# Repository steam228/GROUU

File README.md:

# GROUU - Modular Open Agriculture

## Overview
GROUU enables the implementation of Precision Agriculture / Automation in the context of personal or small scale agricultures.
At the moment, the development goals for GROUU V2 is to implement a local/edge server based on a raspberry pi or other linux mini computer, a sensor node template with wifi communication and other with LoraWAN communication. The same for two actuator templates.
when this basic infrastructure is designed we will apply it to personal contexts in order to test it.
This process will generate new repositores.
This Git repository also archives the personal development and learning process behind the project and research done throught it.

**Let us know if you want to collaborate**

## Table of Contents
1. [GROUU V3 — WellBouy (well-water LoRaWAN node)](#grouu-v3--wellbouy)
1. [GROUU V2](#grouu-v2)
   - [Server Documentation - GROUU Server V2 Configuration](#server-documentation)
   - [Sensor Modules Documentation - GROUU V2 Sensor Modules Configuration](#sensor-modules-documentation)
   - [Actuator Modules Documentation - GROUU V2 Sensor Actuator Configuration](#actuator-modules-documentation)
2. [GROUU V1](#grouu-v1)
   - [Modules V1 - ESP12 Based Version](#modules-v1---esp12-based-version)
   - [Server Configuration - Raspberry Pi Zero W](#server-configuration---raspberry-pi-zero-w)
3. [Archived Projects](#archived-projects)
4. [References](#references)

## GROUU V3 — WellBouy

A well-water-quality LoRaWAN sensor node (**XIAO ESP32-S3 + Wio-SX1262**): reads
water **temperature / TDS / turbidity / pH**, encodes them as CayenneLPP, and
uplinks to **The Things Network** (EU868, OTAA) while deep-sleeping between
readings. On a **Raspberry Pi** the data flows TTN → Node-RED → InfluxDB 2 →
Grafana, and a small public dashboard renders it live.

📁 [/ARDUINO/GROUU_V3/](/ARDUINO/GROUU_V3/) · 📊 live dashboard: **https://grouuwell01.hacktoimprove.com**

Full docs — hardware, firmware bring-up, calibration, data pipeline, the web
dashboard, and the dedicated atopile PCB — are in
[ARDUINO/GROUU_V3/README.md](/ARDUINO/GROUU_V3/README.md).

## GROUU V2

### Sensor Modules Documentation
GROUU V2 Sensor Modules Configuration

[/ARDUINO/GROUU_V2/](/ARDUINO/GROUU_V2/)

#### GROUU V2 WiFi Sensor Node Template

#### GROUU V2 LoRA Sensor Node Template

### Actuator Modules Documentation
GROUU V2 Sensor Actuator Configuration

### Server Documentation
GROUU Server V2 Configuration(GROUU Stack V1)

The GROUU Stack V1 (part of GROUU V2) provides an advanced foundation for your open-source IoT farming project:

1. Mosquitto for MQTT messaging between your farming sensors and the system
2. Node-RED for creating workflows and processing data from your farm
3. InfluxDB for storing time-series data from your agricultural sensors
4. Grafana for creating dashboards to visualize your farming data

#### GROUU Stack V1 Installation and Deployment Tutorial

This guide will help you set up the GROUU Stack V1, an open-source IoT solution for personal and small-scale farming.

##### 1. Install Docker

First, we need to install Docker on your Linux system:

```bash
# Update and upgrade the system
sudo apt update && sudo apt upgrade -y

# Install required packages
sudo apt install -y apt-transport-https ca-certificates curl gnupg lsb-release

# Add Docker's official GPG key and set up the repository
curl -fsSL https://get.docker.com -o get-docker.sh
sudo sh get-docker.sh

# Add your user to the docker group
sudo usermod -aG docker $USER

# Enable Docker to start on boot
sudo systemctl enable docker
```

Log out and log back in for the group changes to take effect.

##### 2. Install Portainer

Now, let's install Portainer:

```bash
# Create volume for Portainer
docker volume create portainer_data

# Install Portainer CE
docker run -d -p 8000:8000 -p 9000:9000 --name=portainer --restart=always \
  -v /var/run/docker.sock:/var/run/docker.sock \
  -v portainer_data:/data \
  portainer/portainer-ce
```

##### 3. Access Portainer

Open a web browser and navigate to `http://your-server-ip:9000`. You'll be prompted to create an admin user.

##### 4. Deploy the GROUU Stack V1

1. In Portainer, go to "Stacks" and click "Add stack".
2. Name your stack "GROUU-Stack-V1".
3. In the "Web editor" tab, paste the GROUU Stack V1 configuration:

```yaml
version: '3'

services:
  mosquitto:
    image: eclipse-mosquitto:latest
    ports:
      - "1883:1883"
    volumes:
      - mosquitto-config:/mosquitto/config
      - mosquitto-data:/mosquitto/data
      - mosquitto-log:/mosquitto/log
    restart: always

  nodered:
    image: nodered/node-red:latest
    ports:
      - "1880:1880"
    volumes:
      - nodered-data:/data
    restart: always

  influxdb:
    image: influxdb:latest
    ports:
      - "8086:8086"
    volumes:
      - influxdb-data:/var/lib/influxdb
    environment:
      - INFLUXDB_DB=grouudb
      - INFLUXDB_ADMIN_USER=admin
      - INFLUXDB_ADMIN_PASSWORD=grouuadmin  # Remember to change this password
    restart: always

  grafana:
    image: grafana/grafana:latest
    ports:
      - "3000:3000"
    volumes:
      - grafana-data:/var/lib/grafana
    restart: always

volumes:
  mosquitto-config:
  mosquitto-data:
  mosquitto-log:
  nodered-data:
  influxdb-data:
  grafana-data:
```

4. Click "Deploy the stack".

##### 5. Post-Deployment Steps

After deploying the GROUU Stack V1, you can access its components:

1. Node-RED (for flow-based programming): `http://your-server-ip:1880`
2. InfluxDB (time-series database): Use the InfluxDB CLI or API at `http://your-server-ip:8086`
3. Grafana (for visualization): `http://your-server-ip:3000`
4. Mosquitto (MQTT broker): Use an MQTT client to connect to `your-server-ip:1883`

Remember to replace `your-server-ip` with your actual server IP address.

##### 6. Security Considerations

- Change default passwords for all services in the GROUU Stack V1
- Use SSL/TLS for MQTT if exposing your farming data to the internet
- Set up proper firewalls and access controls
- Regularly update all containers and the host system to ensure your farming data remains secure

Congratulations! You now have the GROUU Stack V1 up and running for your personal or small-scale farming IoT project.

#### Manual Installation Guide

If you prefer not to use the stack configuration, you can follow these steps for manual installation:

#### 1. Install Docker

Follow the Docker installation steps from the stack installation guide above.

#### 2. Install Portainer CE and Portainer Agent

```bash
# Create volume for Portainer
docker volume create portainer_data

# Install Portainer CE
docker run -d -p 8000:8000 -p 9000:9000 --name=portainer --restart=always -v /var/run/docker.sock:/var/run/docker.sock -v portainer_data:/data portainer/portainer-ce

# Install Portainer Agent
docker run -d -p 9001:9001 --name portainer_agent --restart=always -v /var/run/docker.sock:/var/run/docker.sock -v /var/lib/docker/volumes:/var/lib/docker/volumes portainer/agent
```

#### 3. Install Containers via Portainer

Access Portainer web interface at `http://your-server-ip:9000` and follow these steps for each container:

##### 3.1 Mosquitto (MQTT Broker)

1. Go to "Containers" > "Add container"
2. Name: mosquitto
3. Image: eclipse-mosquitto:latest
4. Port mapping: 1883:1883
5. Volumes:
    - /path/to/mosquitto/config:/mosquitto/config
    - /path/to/mosquitto/data:/mosquitto/data
    - /path/to/mosquitto/log:/mosquitto/log

##### 3.2 Node-RED

1. Go to "Containers" > "Add container"
2. Name: nodered
3. Image: nodered/node-red:latest
4. Port mapping: 1880:1880
5. Volumes:
    - /path/to/nodered/data:/data

##### 3.3 InfluxDB

1. Go to "Containers" > "Add container"
2. Name: influxdb
3. Image: influxdb:latest
4. Port mapping: 8086:8086
5. Volumes:
    - /path/to/influxdb/data:/var/lib/influxdb
6. Environment variables:
    - INFLUXDB_DB=mydb
    - INFLUXDB_ADMIN_USER=admin
    - INFLUXDB_ADMIN_PASSWORD=adminpassword

##### 3.4 Grafana

1. Go to "Containers" > "Add container"
2. Name: grafana
3. Image: grafana/grafana:latest
4. Port mapping: 3000:3000
5. Volumes:
    - /path/to/grafana/data:/var/lib/grafana

#### 4. Post-Installation Steps

Follow the post-deployment steps and security considerations from the stack installation guide above.

## GROUU V1

### Modules V1 - ESP12 Based Version
*Under development - design (boards, enclosures), firmware (Arduino)*

#### Types:
- Core
- S modules (wireless sensors)
- A modules (actuator modules)

#### Development Goals
- The way the module is powered is not yet fully defined: All should have batteries (3.3V _____ Amps), some should have only this as power source and be periodically charged (induction most probably), and others, can be connected to a power source (solar, network, wind...) for constant charging;
- A power source (ex: solar panel) can be a module on its own and an induction charger can be another module (tbd - to be designed);
- The following code:
```cpp
const String Instalation = "myFarm"; //Where is it?
const String IDCODE = "1"; //number your probe
const String TYPE = "SoilProbe"; //choose type
const String Host = "Grouu" + Instalation + TYPE + IDCODE; //just change if it is not grouu and you're adapting the code for something else
const char * OTA_PASSWORD  = "yourpasswordhere";
```
will allow you to set a hostname (Host) - These are the only parameters you should have to change before injecting the firmware on your board (we should work on an even simpler method);

- This hostname (`const String Host`):
  1. will be the name of the network the device generates each time it is not able to connect to any wireless network;
  2. Will identify the MQTT addresses being used by that type of device (expl: `HostName/Sensor/Moist1`);

- There shouldn't be a limit for the amount of modules developed nor used. The scale and context should dictate these options.
- All Explorations, independently from the context or scale should be considered valid data generators;

#### Call for Collaboration

It is permanent, develop whatever you want whenever you want!

#### Current Modules

##### Soil Probe

- The soil probe reads Soil Moisture and Soil Temperature;
- You can add as many as you want in order to measure these in as many points as you wish.

###### Design
- eagleCAD: [Link to eagleCAD files]
- Fusion 3D (plastic 3D print Enclosure): [Link to Fusion 3D files]

###### Code
- Arduino IDE Firmware: [Link to Arduino code]

##### Water Router

- The water router uses a standard 1 in 4 out electrovalves from a washing machine. You should also decrease the water pressure on the outputs for microirrigation.
- You can use this directly to the network or after a motor (be careful with the pressure in compatibility). You can add as many as you want in the system.

###### Design
- eagleCAD: [Link to eagleCAD files]
- Fusion 3D (plastic 3D print Enclosure): [Link to Fusion 3D files]

###### Code
- Arduino IDE Firmware: [Link to Arduino code]

##### Core

- Core is the local server. Right now is mostly a test hub where the data from the networked servers is received and processed.
- We are using Node-Red but all collaboration is welcomed!

###### Design
Right now we are using a standard Raspberry case.

### Server Configuration - Raspberry Pi Zero W

#### Configuring Raspberry Pi Zero W as server

1. Configuring the Pi: [Tutorial Link](https://core-electronics.com.au/tutorials/raspberry-pi-zerow-headless-wifi-setup.html)

2. Accessing through ssh on mac or linux terminal: [Tutorial Link](https://www.raspberrypi.org/documentation/remote-access/ssh/unix.md)

3. Upgrade Node-Red and Node.js
```bash
sudo apt-get update
sudo apt-get upgrade
bash <(curl -sL https://raw.githubusercontent.com/node-red/raspbian-deb-package/master/resources/update-nodejs-and-nodered)
sudo systemctl enable nodered.service
```
- Connect to Raspberry Pi Node-red console through your browser by accessing `http://"raspipaddress":1880`

- Install Mosquitto MQTT broker
```bash
sudo apt-get install mosquitto
```

Some instructions on how to test here: [Instructables Tutorial](https://www.instructables.com/id/Installing-MQTT-BrokerMosquitto-on-Raspberry-Pi/)

4. Other useful links:
   Security: manage permissions on node-red tutorial - [YouTube Tutorial](https://www.youtube.com/watch?v=GeN7g4bdHiM)

## Archived Projects

### Main Soil Probe REV0
Developed at the Habibi Works (Ioannina, Greece) CultiMake Workshop - P2PLab

#### Design
- eagleCAD: A provisional board (not working!!) is on [/BOARDS/soilProbe/Archive](/BOARDS/soilProbe/Archive)
- For this example, a nodeMCU dev board was used and tested at the workshop (see Habibi.Works [Workshop Journal](WORKSHOP/habibiWorksJuly2018/workshopJournal.md))
- Enclosure: A standard plastic box was used for demo purposes.

This board includes:
- 1 x 4 male header for DHT22 Temperature and Humidity Sensor
- 1 x 3 male header for DS18B20 (encapsulated version for Soil Temperature)
- 2 x 2 male header connections for Moisture 10k with Two probes
- 1 led (no usage yet, mostly for debug purposes)
- 1 ftdi set headers
- 1 voltage converter 12V - 3,3V
- 1 x 2 screw headers to add solar panel + battery (maybe connect solar battery pack now)

#### Code
Arduino IDE Firmware: [/ARDUINO/habibiWorksJuly2018-WS/grouu-irr](/ARDUINO/habibiWorksJuly2018-WS/grouu-irr)

### GROUU Greenhouse

#### Design
- SolidWorks files for the complete Structure (to be added) - also check constructive system (levosystems.com)
- Photos (soon)
- Other Diagrams (soon)

#### Code
Arduino Yun code: [/ARCHIVE/arduino/GROUU_GREENHOUSE_0/](/ARCHIVE/arduino/GROUU_GREENHOUSE_0/)

## References

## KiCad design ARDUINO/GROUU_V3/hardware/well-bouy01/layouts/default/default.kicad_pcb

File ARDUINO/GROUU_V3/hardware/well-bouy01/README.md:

# well-bouy01

Wooohooo a new package!

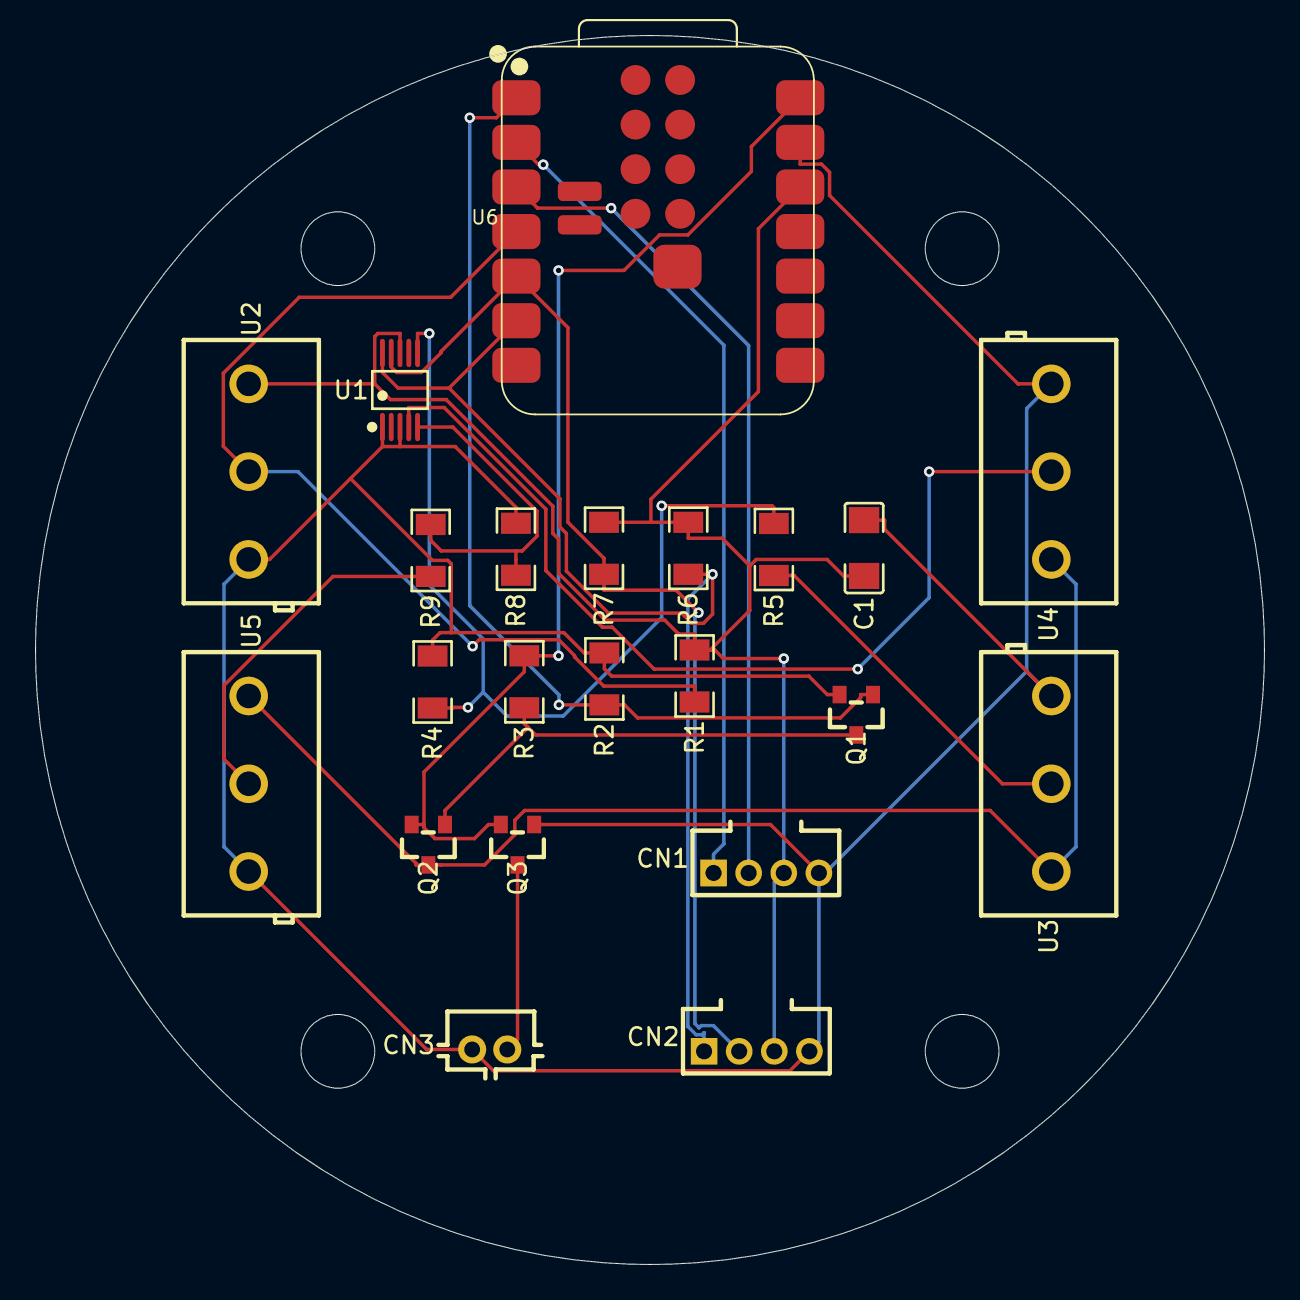
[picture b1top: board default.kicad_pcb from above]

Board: 2 copper layers, 70.0 x 70.0 mm, 22 parts (0 on the bottom side), 17 nets.

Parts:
C1: 100nF ±10%; C1206
CN1, CN2: CONN-TH_4P-P2.00_L5.1-W10.0
CN3: CONN-TH_B2B-PH-K-S
Q1, Q2, Q3: SOT-23_L2.9-W1.3-P1.90-LS2.4-BR
R1, R6, R7: 4.7kΩ ±1%; R1206
R2, R3: 100kΩ ±5%; R1206
R4: 18kΩ ±1%; R1206
R5, R9: 10kΩ ±1%; R1206
R8: 6.8kΩ ±1%; R1206
U1: MSOP-10_L3.0-W3.0-P0.50-LS5.0-BL
U2, U3, U4, U5: CONN-TH_3P-P5.00_KF301-5.0-3P
U6: XIAO-ESP32-S3-SMD_PAD

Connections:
1: CN1.1, U6.2
1-1: Q2.3, U3.1, U4.1, U5.1
2: CN1.2, U6.3
5: R8.1, R9.2, U1.5
6: R4.1, R5.2, U1.6
S: Q2.2, Q3.2, R3.2, U6.14
ds_data: R1.1, U2.2, U6.4
hv: C1.1, CN1.3, CN2.3, R1.2, R6.2, R7.2, U1.8, U2.1, U6.12
lv: C1.2, CN1.4, CN2.4, CN3.2, Q1.2, Q3.1, R2.2, R4.2, R8.2, U1.1, U1.3, U2.3, U3.3, U4.3, U5.3, U6.13
pfet_gate: Q1.3, Q2.1, R3.1
ph_in: R5.1, U3.2
scl: CN2.1, R6.1, U1.10, U6.6
sda: CN2.2, R7.1, U1.9, U6.5
sensor_pwr_en: Q1.1, R2.1, U6.1
tds_in: U1.4, U4.2
turb_in: R9.1, U5.2
v5v_raw: CN3.1, Q3.3

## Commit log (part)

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2014-01-29 Basecode
2014-01-29 w/libraries
2014-01-29 serial formula
2014-09-02 Ultimas
2016-06-24 site e organização
    Nova Fase!!!
2016-06-26 organising gitsss
2016-07-11 organic site
2016-10-14 solved form issues
    integration of ajax form complete
2016-10-14 w/landing page
2016-10-15 new alpha on p5js overlay
2016-10-27 last
2016-11-18 organização
2016-11-30 correct minor
2018-07-21 new board
2018-07-21 added readme with notes for documentation
2018-07-25 arranjo pastas
2018-07-26 placa com headers thanks to FS
2018-07-27 last - mill.headers production
2018-07-27 conflict
2018-07-29 readme notes!
2018-07-31 BH, materials and workshop HW
2018-07-31 day3 closed
2018-08-01 bug fix 1
2018-08-01 readme
2018-08-23 end of workshop
2018-09-01 new data
2018-09-01 logo on readme
2018-09-01 restOfPhotos
2018-09-01 organised readme
2018-09-01 organised readme2
2018-09-01 organised readme3
2018-09-01 organised readme4
2018-09-01 organised readme5
2018-09-01 organised readme6
2018-09-01 organised readme7
2018-09-01 organised readme8
2018-09-01 organised readme9
2018-09-01 organised readme10
2018-09-01 organised readme11
2018-09-01 organised readme12
2018-09-01 housekeeping over
2018-09-03 new Scheme SoilProbe
2018-09-04 readme updates
2018-09-04 readme errors
2018-09-05 diagramns
2018-09-10 presentation tech fest
2019-02-01 componentesPT
2019-02-02 readme componentes para alunos
2019-03-05 Set theme jekyll-theme-minimal
2019-03-05 pages
2019-03-05 pages2
2019-03-05 pages3
2019-03-05 Set theme jekyll-theme-tactile
2019-03-05 pages4
2019-06-06 last 2nd day
2019-06-07 missing value stability
2021-08-16 [ImgBot] Optimize images
    *Total -- 16,056.03kb -> 12,599.25kb (21.53%)
    /docs/Set V0 GROUU/Screenshot_2019-01-30 US $1 11 15% OFF 100V Liquid Water Level Sensor Horizontal Float Switch For Aquariums Fish Tank-in Fl....png -- 87.23kb -> 31.43kb (63.97%)
    /docs/Set V0 GROUU/Screenshot_2019-01-30 US $1 11 15% OFF 100V Liquid Water Level Sensor Horizontal Float Switch For Aquariums Fish Tank-in Fl... 2.png -- 87.23kb -> 31.43kb (63.97%)
    /docs/Set V0 GROUU/Screenshot 2019-02-02 at 19.34.35.png -- 131.61kb -> 65.06kb (50.56%)
    /images/router.png -- 4.05kb -> 2.02kb (50.26%)
    /images/core.png -- 4.02kb -> 2.07kb (48.63%)
2024-07-08 platformio grouu v2 versions first commit
2024-07-08 added header.h
2024-07-08 added header.h 2
2024-07-09 lorawan-platformio-basicnodecode
2024-07-10 new stuff
2024-07-12 actualizcoes nodes
2024-07-18 server docs
2024-07-18 cleared readme
2024-07-18 cleared readme2
2024-07-18 cleared readme3
2024-07-18 cleared readme4
2024-07-18 cleared readme5
2024-07-18 cleared readme6
